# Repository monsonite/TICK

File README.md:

# TICK

A minimalist 8-bit "TTL" microcomputer based on a bit-serial ALU.

TICK is a variation of THE 16-bit MITE, bit serial machine.

The Accumulator and RAM bus have been truncated to 8-bits. However the Program Counter and the B-Register remain at 16-bits wide.

MITE provided the test bed for the discrete logic and bit-serial ALU, and TICK further refined the ALU, Program Counter and timing pulse generator into just a 6 package module, and equipped it with 8-bit parallel interfaces, suitable for connecting with a standard parallel, tristate memory data bus.

Only so much can be some in the "Digital" simulator, so now the design is being built up on breadboard, usings currently available 74HCxx series logic devices.

This will include an efficient, parallel memory sub-section, to accompany the compact TICK bit serial ALU and a means of emulating the ROM and programming the contents of the SRAM using an Arduino NANO or Raspberry Pi Pico - or clone.

The 28 ICs used are as follows:

U1	AT27C1024 	ROM

U2	74HC595		PC LOW

U3	74HC595		PC HIGH

U4	74HC165		B LOW

U5 	74HC165		B HIGH

U6	74HC4060	CLOCK DIV

U7	74HC00		SR LATCH

U8	74HC161		SEQUENCE COUNTER	

U9	74HC175		SEQUENCE FLIP FLOPS

U10	74HC138		INSTRUCTION DECODER

U11	74HC11		DECODE LOGIC	

U12	74HC85		DECODE LOGIC

U13	74HC00		DECODE LOGIC

U14	74HC283		FULL ADDER / PC INCREMENTER

U15	74HC126		ALU MUX/ PC MUX

U16	74HC74		CARRY FF / PC FF

U17	74HC299		ACCUMULATOR

U18	62256		RAM

U19	74HC74		CARRY FF / ZERO FF

U20	74HC00		RAM CONTROL

U21	74HC74		ZERO & CARRY FLAGS

U22	74HC595		SPI INPUT REGISTER

U23	74HC153		CONDITION DECODER

U24	74HC125		BUFFER

U25	74HC125		BUFFER

U26	74HC595		ROMULATOR

U27	74HC595		ROMULATOR

U28	74HC00		SPARE

## TICK - An Experimental 8-bit Bit Serial CPU.

TICK is an 8-bit, bit serial machine, with a modified Harvard architecture. This means that a ROM provides instructions and data, and volatile storage of variables is from RAM - in this case a 32K x 8-bit SRAM. ROM and RAM have separate datapaths and separate ddress buses.

TICK is based around a bit-serial architecture, consisting of an ALU, an Accumulator AC, a Memory Buffer Register B, and a Program Counter PC.

In addition to the registers there are functional blocks of the Clock Sequencer and Timing Pulse Generator CS and TPG.

The advantage of the bit-serial design is that it can easily be extended from 8-bits to 16-bits or even 32 bits with very little additional hardware.

TICK is an experimental machine, and with only about 20 ICs, it may be prototyped onto about 8 standard breadboards, or fit onto a low-cost 10 x 10 cm pcb.

Breadboard #1	ALU and Carry flip-flop

Breadboard #2	Clock oscillator, clock sequencer and timing pulse generator

Breadboard #3	Accumulator AC, Zero Detector, Zero flag, control and jump logic

Breadboard #4	Memory Buffer Register MB

Breadboard #5	Memory Address Register MA

Breadboard #6	Program Counter PC, SRAM 

Breadboard #7	Input/Output

Breadboard #8	Expansion and interface to Arduino Nano - for programming

By putting the pricipal registers AC, PC, MB on their own breadboard, it means that they can easily be extended to 16-bit or 32- bit wordlength, just by "daisy-chaining" more shift register packages in a row, and modifying the clock sequencer for a longer bit-sequence.

1. ALU and Carry Flipflop

2. Clock Sequencer and Timing Generator.

This section is the timing generator at the top 4017 decade counter and 74xx00 acting as SR latch. The actual prototype will also use a 74HC4060 14 stage counter to act as clock generator.

In the middle is the ALU. This a much tried and tested design consisting of a 74xx86 quad 2-input XOR and a pair of 74xx00 quad 2-input NANDs.

The first pair of XOR gates allow the A and B inputs to be selectively inverted for subtraction, negation and some of the logic "inverse" functions.
The next pair of XORs and NANDs form a full adder to give the Sum and Carry produced from the A and B inputs.

Three NAND gates forms a multiplexer, to choose between the Sum of A and B (A XOR B) and the Carry (A AND B). These are re-used as the logical operations.

During a logical operation, and Carry should be suppressed - hence another pair of NANDs.

Any Carry generated is retained in the 74HC74 flipflop U12A. It is then presented to the ALU when the next pair of bits are added together - so it can be included in the sum.
At the bottom in U15 and U16 is a half adder. This is used to increment the program counter after each instruction or jump to a new address. 

Any carry generated by the PC is handled in the other half of the D-type flipflop U12B.

Apart from the counters and flipflops - much of this sheet is combinational logic and could easily be replaced by a look-up table in a very small PROM.

3. Program Counter.

The 16-bit Program Counter is based around a pair of 74HC595 shift registers.

They are combined with the half adder - on the ALU sheet, so that they increment every instruction cycle, or can be loaded from serial data from the Accumulator.

The output is a 16-bit parallel word used to address the SRAM.

It could be argued that the parallel output register in the 74HC595 is doubling up as the Memory Address register MA.

The 74HC595 is a very versatile chip for interfacing to parallel RAM or parallel peripherals.

4. Memory Buffer Register MB and Switch Register SR

This is  the "Switch Register" and the "B" Shift Register which is a 74HC165 U3.

In the simulator the switches are just a convenient way to enter a byte of data - just like the front panel switches on old minicomputers.

The 74HC165 loads in the parallel word at the start of each instruction cycle and converts it to the serial pulse train Bout - which is then fed into the ALU.

5. Accumulator AC

The 8-bit Accumulator based around a single 74HC595 8-bit shift register.

If you want a 16-bit machine you just chain another 74HC595 in series with this.

It is a versatile shift register because it has a parallel output latch, so you can store the final result in parallel form - possibly for writing to a memory bus.

Fout is the 8-bit serial function that is output from the ALU.

Aout is the output of the Accumulator which is recirculated through the ALU, for example during addition.

T8 is the ninth timing pulse (they start at T0). It latches the contents of the Accumulator shift-register onto the parallel bus at the end of the completed instruction cycle.

The diode array is just an 8-input OR, it is used to detect zero.

6. Instruction Decoder.

This the Instruction Decoder - this was inspired by Marcel van Kervinck who created the Gigatron kit.

It is essentially a tiny ROM based on a diode matrix.

The instruction field is only 3 bits wide, needed to encode the 8 possible instructions.

These three bits are fed into U1 - which is a 74HC138, 3-8 line decoder.

The 3 bit input cause one of the outputs of the 74HC138 to go to logic low, the rest remaining high. From the image you can see that the 8 outputs identify the individual instruction group. Some instructions have multiple options such as choice of operands, destination etc.

LOAD

AND

OR

XOR

ADD

SUB

STORE

JUMP

Further instructions may be added later by decoding a fourth instruction bit.

In the image I apply the ADD instruction 100 in binary.

The 74HC138 selects one horizontal line of the ROM and any diodes connected to that line are pulled low. The resulting bit pattern is fed to U2 which is a 74HC540 octal inverter/driver.

This converts the instruction into a 7-bit pattern, in this case 21H.

The 7 bits define the control signals that are applied to the ALU, such as Carry, I0 and I1 select which function is chosen by the ALU output multiplexer, as follows.

00 Zero

01 XOR

10 AND

11 OR

Zero is a good way to clear the Accumulator before starting a new operation.

This circuit is entirely combinational and could be reduced to a look up table included in the same small PROM that holds the ALU.

As the ALU has 7 input control signals there are theoretically 128 possible instructions - this decoder just picks the most useful 8!

# Update 28-04-24

Some more progress on the MITE bit serial computer.

I can now load the Memory Buffer (MB) register from RAM, in parallel, and then with the one press of a single stepping switch it copies its contents into the Accumulator.

The serial output of the MB register goes directly to the serial input of the Accumulator.  The next stage is to pass this output through the ALU so that can be tested.

Below is the overall view of the device which now takes up 7, sparsely populated breadboards.

The IC count is 17 74HCxx packages and the SRAM. One of the Arduinos will be retained as the laptop interface to the computer memory.
You will have to open the image to view all the boards.

From the top:

1. LED bar displays to show the contents of the MB register (left) and the Accumulator (right).
 
2. MB (74HC165) left and Accumulator (74HC595) right.

3. SRAM Access. 62256 SRAM, 74HC245 bi-directional tristate buffer, 2 x 74HC595 ( Memory Access Register/ PC) Arduino support module to allow access to contents of RAM.
 
4. LED bar displays to show the contents of the address and data registers. MAR and external bus.
 
5. Clock pulse generator and timing. A 74HC4060 is an oscillator with a 14-stage binary divider. I am currently only clocking it at around 500Hz - so I can see what is happening. You can choose whichever clock division ratio you wish.

The 74HC4060 feeds a 74HC4017 which is a decoded, decade counter. This produces a gating signal that allows a trains of 8 clock pulses to be sent to the shift-registers to co-ordinate their data exchanges.

6. ALU termination connectors and another Arduino module to machine test the ALU.
The ALU has 8 inputs, of which 3 are the Ain, Bi and Cin from the shift registers
The Arduino is just a convenient way to dial in an instruction and test data to ensure the output is correct.

7. ALU and PC incrementer, plus any additional combinational glue logic. The PC consists of a pair of 74HC595 shift registers incremented or loaded from the MB register - in a jump condition.

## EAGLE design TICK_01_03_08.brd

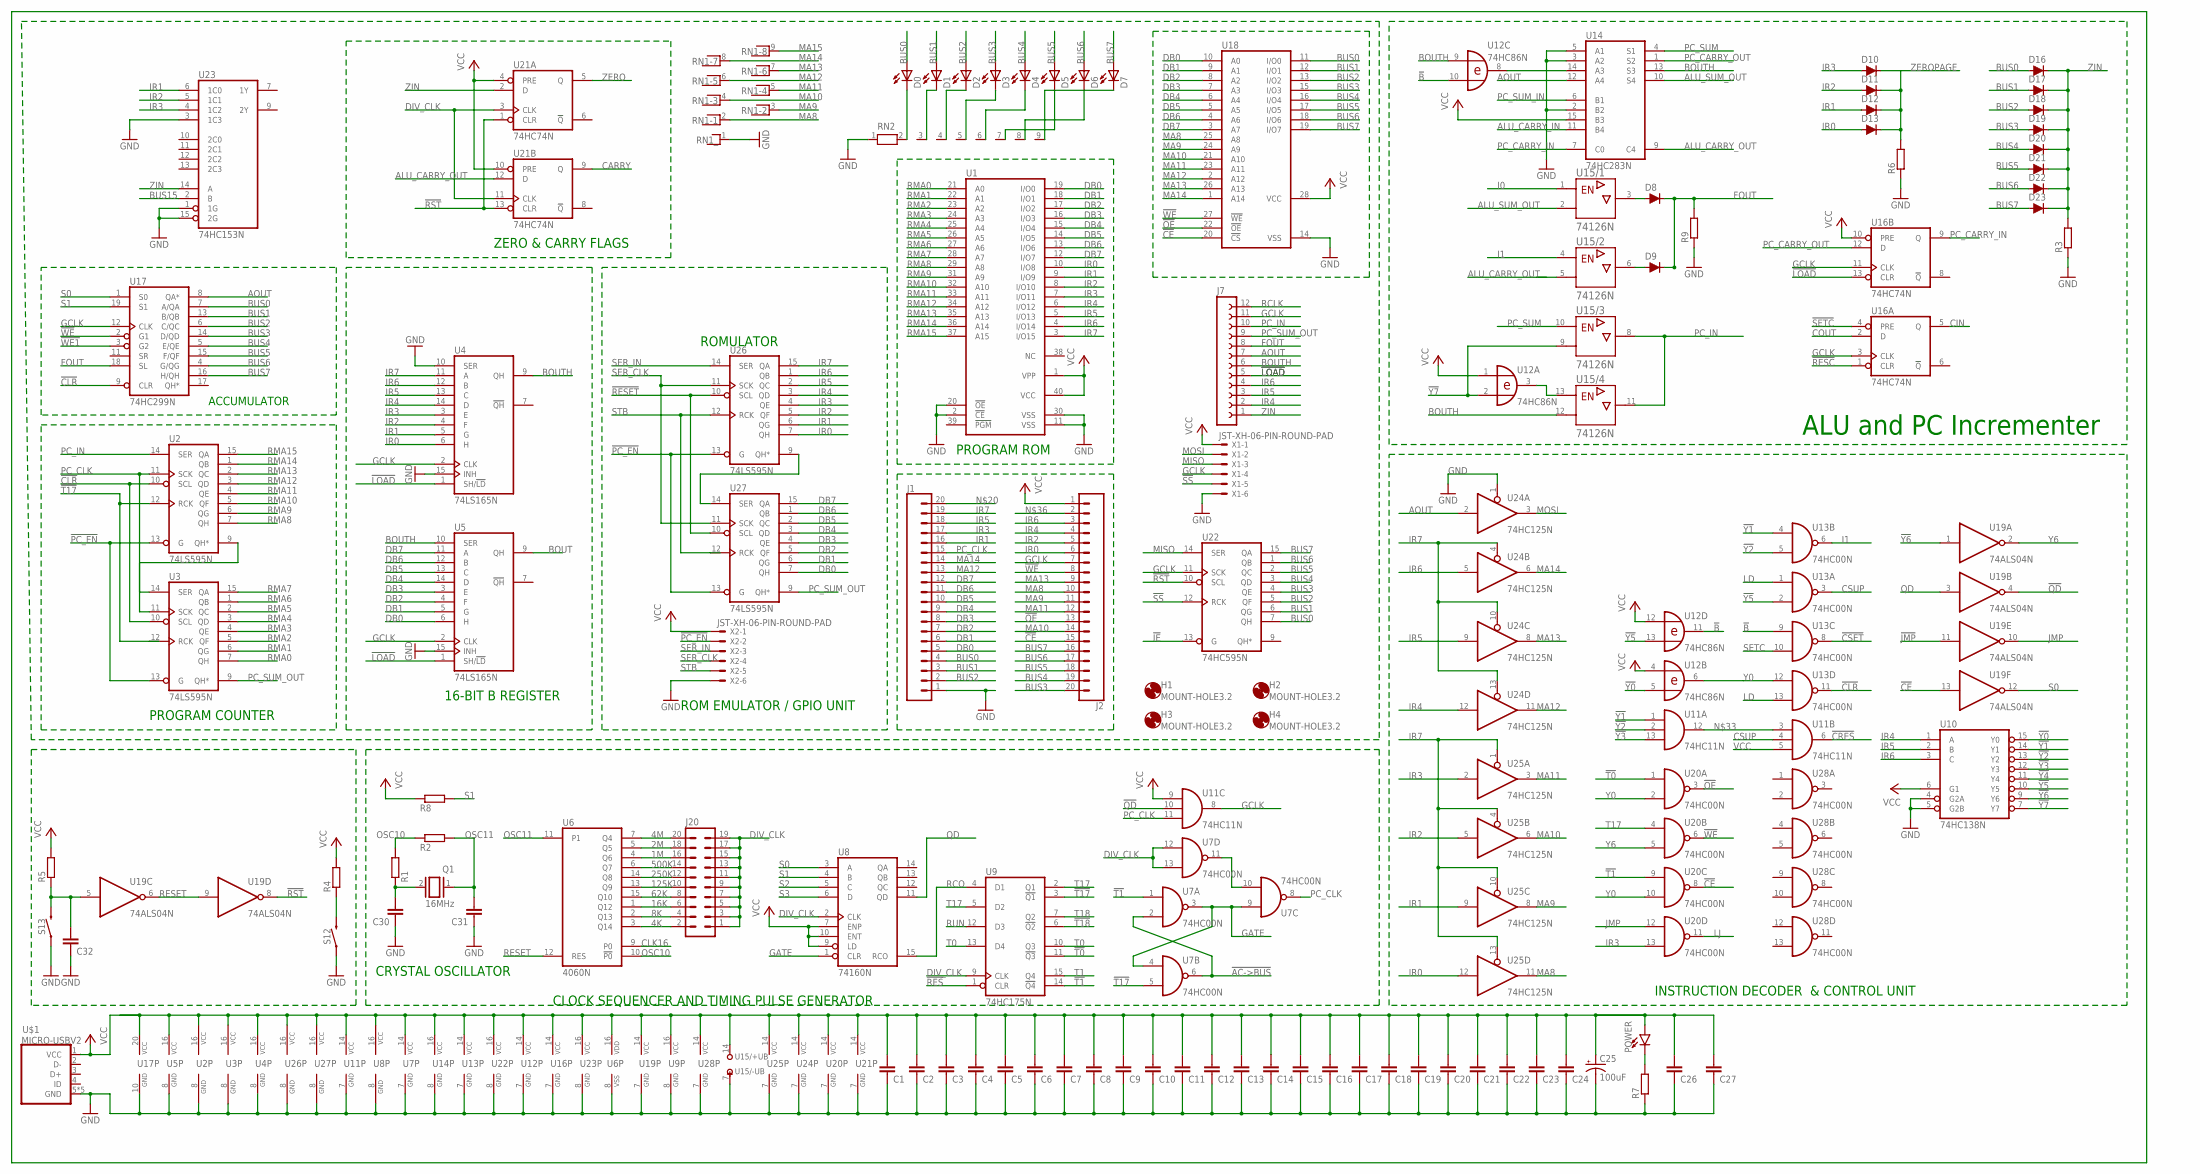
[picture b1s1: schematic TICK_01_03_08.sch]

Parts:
C1, C2, C3, C4, C5, C6, C7, C8, C9, C10, C11, C12, C13, C14, C15, C16, C17, C18, C19, C20, C21, C22, C23, C24, C26, C27, C30, C31, C32: C-EU025-024X044; C025-024X044
C25: 100uF; CPOL-RADIAL-2.5MM-6.5MM
D0, D1, D2, D3, D4, D5, D6, D7: LED3MM
D8, D9, D10, D11, D12, D13, D17, D18, D19, D20, D21, D22, D23: 200mA/100V/1V; DIODE-1N4148
D16: 200mA/100V/1V; DIODE-1N4148-KIT
H1, H2, H3, H4: MOUNT-HOLE3.2; 3,2
J1, J2: CONN_20NO_SILK_KIT; 1X20_NO_SILK_KIT
J7: FE12-1; FE12
J20: MA10-2
POWER: LED3MM; LED_3MM
Q1: 16MHz; QS
R1, R2, R3, R4, R5, R6, R7, R8, R9: R-EU_0204/5; 0204/5
RN1: RNX8; RN-9
RN2: RN08; RN-9
S12, S13: MOMENTARY-SWITCH-SPST-PTH-6.0MM; TACTILE_SWITCH_PTH_6.0MM
U1: 27C1024HG; DIL40
U2, U3, U26, U27: 74LS595N; DIL16
U4, U5: 74LS165N; DIL16
U6: 4060N; DIL16
U7, U13, U20, U28: 74HC00N; DIL14
U8: 74160N; DIL16
U9: 74HC175N; DIL16
U10: 74HC138N; DIL16
U11: 74HC11N; DIL14
U12: 74HC86N; DIL14
U14: 74HC283N; DIL16
U15: 74126N; DIL14
U16, U21: 74HC74N; DIL14
U17: 74HC299N; DIL20
U18: 62256P; DIL28-6
U19: 74ALS04N; DIL14
U22: 74HC595N; DIL16
U23: 74HC153N; DIL16
U24, U25: 74HC125N; DIL14
U$1: MICRO-USBV2; MICRO-USB-2
X1, X2: JST-XH-06-PIN-ROUND-PAD; JST-XH-06-PACKAGE-ROUND-PAD

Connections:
1M: J20.16, U6.4 (Q6)
2M: J20.18, U6.5 (Q5)
4K: J20.2, U6.3 (Q14)
4M: J20.20, U6.7 (Q4)
8K: J20.4, U6.2 (Q13)
16K: J20.6, U6.1 (Q12)
62K: J20.8, U6.15 (Q10)
125K: J20.10, U6.13 (Q9)
250K: J20.12, U6.14 (Q8)
500K: J20.14, U6.6 (Q7)
!AC->BUS: U7.2 (I1), U7.6 (O)
!B: U12.10 (I1), U12.11 (O), U13.9 (I0)
!CE: J2.15, U18.20 (!CS), U19.13 (I), U20.8 (O)
!CLR: U2.10 (SCL), U3.10 (SCL), U13.11 (O), U17.9 (CLR)
!CRES: U11.6 (O)
!CSET: U13.8 (O)
!IE: U22.13 (G)
!JMP: U19.11 (I)
!LOAD: J7.5, U4.1 (SH/!LD), U5.1 (SH/!LD), U16.13 (CLR)
!OE: J2.13, U18.22 (!OE), U20.3 (O)
!PC_EN: U2.13 (G), U3.13 (G), U26.13 (G), U27.13 (G), X2.2
!QD: U11.10 (I1), U19.4 (O)
!RES: U9.1 (CLR)
!RESC: U16.1 (CLR)
!RESET: U26.10 (SCL), U27.10 (SCL)
!RST: U19.8 (O), U21.1 (CLR), U21.13 (CLR), U22.10 (SCL)
!SETC: U16.4 (PRE)
!SS: U22.12 (RCK), X1.5
!T0: U9.11 (!Q3), U20.1 (I0)
!T1: U7.1 (I0), U9.14 (!Q4), U20.9 (I0)
!T17: U2.12 (RCK), U3.12 (RCK), U7.5 (I1), U9.3 (!Q1)
!T18: U9.6 (!Q2)
!WE: J2.8, U17.2 (G1), U18.27 (!WE), U20.6 (O)
!WE1: U17.3 (G2)
!Y0: U10.15 (Y0), U12.5 (I1)
!Y1: U10.14 (Y1), U11.1 (I0), U13.4 (I0)
!Y2: U10.13 (Y2), U11.2 (I1), U13.5 (I1)
!Y3: U10.12 (Y3), U11.13 (I2)
!Y4: U10.11 (Y4)
!Y5: U10.10 (Y5), U12.13 (I1), U13.2 (I1)
!Y6: U10.9 (Y6), U19.1 (I)
!Y7: U10.7 (Y7), U12.2 (I1), U15.9 (A)
ALU_CARRY_IN: U14.11 (B4)
ALU_CARRY_OUT: U14.9 (C4), U15.5 (A), U21.12 (D)
ALU_SUM_OUT: U14.10 (S4), U15.2 (A)
AOUT: J7.7, U14.12 (A4), U17.8 (QA*), U24.2 (I)
BOUT: U5.9 (QH)
BOUTH: J7.6, U4.9 (QH), U5.10 (SER), U12.9 (I0), U14.13 (S3), U15.12 (A)
BUS0: D0.A, D16.A, J1.4, U17.7 (A/QA), U18.11 (I/O0), U22.7 (QH)
BUS1: D1.A, D17.A, J1.3, U17.13 (B/QB), U18.12 (I/O1), U22.6 (QG)
BUS2: D2.A, D18.A, J1.2, U17.6 (C/QC), U18.13 (I/O2), U22.5 (QF)
BUS3: D3.A, D19.A, J2.20, U17.14 (D/QD), U18.15 (I/O3), U22.4 (QE)
BUS4: D4.A, D20.A, J2.19, U17.5 (E/QE), U18.16 (I/O4), U22.3 (QD)
BUS5: D5.A, D21.A, J2.18, U17.15 (F/QF), U18.17 (I/O5), U22.2 (QC)
BUS6: D6.A, D22.A, J2.17, U17.4 (G/QG), U18.18 (I/O6), U22.1 (QB)
BUS7: D7.A, D23.A, J2.16, U17.16 (H/QH), U18.19 (I/O7), U22.15 (QA)
BUS15: U23.2 (B)
CARRY: U21.9 (Q)
CIN: U16.5 (Q)
CLK16: U6.9 (P0)
COUT: U16.2 (D)
CSUP: U11.4 (I1), U13.3 (O)
DB0: J1.5, U1.19 (I/O0), U5.6 (H), U18.10 (A0), U27.7 (QH)
DB1: J1.6, U1.18 (I/O1), U5.5 (G), U18.9 (A1), U27.6 (QG)
DB2: J1.7, U1.17 (I/O2), U5.4 (F), U18.8 (A2), U27.5 (QF)
DB3: J1.8, U1.16 (I/O3), U5.3 (E), U18.7 (A3), U27.4 (QE)
DB4: J1.9, U1.15 (I/O4), U5.14 (D), U18.6 (A4), U27.3 (QD)
DB5: J1.10, U1.14 (I/O5), U5.13 (C), U18.5 (A5), U27.2 (QC)
DB6: J1.11, U1.13 (I/O6), U5.12 (B), U18.4 (A6), U27.1 (QB)
DB7: J1.12, U1.12 (I/O7), U5.11 (A), U18.3 (A7), U27.15 (QA)
DIV_CLK: J20.1, J20.3, J20.5, J20.7, J20.9, J20.11, J20.13, J20.15, J20.17, J20.19, U7.12 (I0), U7.13 (I1), U8.2 (CLK), U9.9 (CLK), U21.3 (CLK), U21.11 (CLK)
FOUT: D8.C, D9.C, J7.8, R9.2, U17.18 (SL)
GATE: U7.3 (O), U7.4 (I0), U7.9 (I0), U8.1 (CLR)
GCLK: J2.7, J7.11, U4.2 (CLK), U5.2 (CLK), U11.8 (O), U16.3 (CLK), U16.11 (CLK), U17.12 (CLK), U22.11 (SCK), X1.4
GND: C1.1, C2.1, C3.1, C4.1, C5.1, C6.1, C7.1, C8.1, C9.1, C10.1, C11.1, C12.1, C13.1, C14.1, C15.1, C16.1, C17.1, C18.1, C19.1, C20.1, C21.1, C22.1, C23.1, C24.1, C25.2 (-), C26.1, C27.1, C30.1, C31.1, C32.1, J1.1, R3.1, R6.1, R7.1, R9.1, RN1.1, RN2.1, S12.1, S13.1, U1.2 (!CE), U1.11 (VSS), U1.20 (!OE), U1.30 (VSS), U2.8 (GND), U3.8 (GND), U4.8 (GND), U4.10 (SER), U4.15 (INH), U5.8 (GND), U5.15 (INH), U6.8 (VSS), U7.7 (GND), U8.8 (GND), U9.8 (GND), U10.4 (G2A), U10.5 (G2B), U10.8 (GND), U11.7 (GND), U12.7 (GND), U13.7 (GND), U14.2 (B2), U14.3 (A2), U14.5 (A1), U14.8 (GND), U15.7 (-UB), U16.7 (GND), U17.10 (GND), U18.14 (VSS), U19.7 (GND), U20.7 (GND), U21.7 (GND), U22.8 (GND), U23.1 (1G), U23.3 (1C3), U23.8 (GND), U23.15 (2G), U24.1 (OE), U24.7 (GND), U25.7 (GND), U26.8 (GND), U27.8 (GND), U28.7 (GND), U$1.5 (GND), U$1.P$1 (GND), U$1.P$2 (GND), U$1.P$3 (GND), U$1.P$4 (GND), X1.6, X2.6
I0: U15.1 (G)
I1: U13.6 (O), U15.4 (G)
IR0: D13.A, J2.6, U1.10 (I/O8), U4.6 (H), U25.12 (I), U26.7 (QH)
IR1: D12.A, J1.16, U1.9 (I/O9), U4.5 (G), U23.6 (1C0), U25.9 (I), U26.6 (QG)
IR2: D11.A, J2.5, U1.8 (I/O10), U4.4 (F), U23.5 (1C1), U25.5 (I), U26.5 (QF)
IR3: D10.A, J1.17, U1.7 (I/O11), U4.3 (E), U20.13 (I1), U23.4 (1C2), U25.2 (I), U26.4 (QE)
IR4: J2.4, J7.2, U1.6 (I/O12), U4.14 (D), U10.1 (A), U24.12 (I), U26.3 (QD)
IR5: J1.18, J7.3, U1.5 (I/O13), U4.13 (C), U10.2 (B), U24.9 (I), U26.2 (QC)
IR6: J2.3, J7.4, U1.4 (I/O14), U4.12 (B), U10.3 (C), U24.5 (I), U26.1 (QB)
IR7: J1.19, U1.3 (I/O15), U4.11 (A), U24.4 (OE), U24.10 (OE), U24.13 (OE), U25.1 (OE), U25.4 (OE), U25.10 (OE), U25.13 (OE), U26.15 (QA)
JMP: U19.10 (O), U20.12 (I0)
LD: U13.1 (I0), U13.13 (I1)
LJ: U20.11 (O)
MA8: J2.10, RN1.2, U18.25 (A8), U25.11 (O)
MA9: J2.11, RN1.3, U18.24 (A9), U25.8 (O)
MA10: J2.14, RN1.4, U18.21 (A10), U25.6 (O)
MA11: J2.12, RN1.5, U18.23 (A11), U25.3 (O)
MA12: J1.13, RN1.6, U18.2 (A12), U24.11 (O)
MA13: J2.9, RN1.7, U18.26 (A13), U24.8 (O)
MA14: J1.14, RN1.8, U18.1 (A14), U24.6 (O)
MA15: RN1.9
MISO: U22.14 (SER), X1.3
MOSI: U24.3 (O), X1.2
unnamed: D0.K (C), RN2.2
unnamed: D1.K (C), RN2.3
unnamed: U7.10 (I1), U7.11 (O)
unnamed: D2.K (C), RN2.4
unnamed: D8.A, U15.3 (Y)
unnamed: R4.1, S12.3 (2)
unnamed: C32.2, R5.1, S13.3 (2), U19.5 (I)
unnamed: POWER.K (C), R7.2
unnamed: U12.8 (O), U14.14 (A3)
unnamed: D9.A, U15.6 (Y)
unnamed: D3.K (C), RN2.5
unnamed: D4.K (C), RN2.6
unnamed: D5.K (C), RN2.7
unnamed: D6.K (C), RN2.8
unnamed: D7.K (C), RN2.9
unnamed: U2.9 (QH*), U3.14 (SER)
unnamed: U11.3 (I0), U11.12 (O)
unnamed: U26.9 (QH*), U27.14 (SER)
unnamed: U12.3 (O), U15.13 (G)
unnamed: C30.2, Q1.2, R1.1
OSC10: R1.2, R2.1, U6.10 (!P0)
OSC11: C31.2, Q1.1, R2.2, U6.11 (P1)
PC_CARRY_IN: U14.7 (C0), U16.9 (Q)
PC_CARRY_OUT: U14.1 (S2), U16.12 (D)
PC_CLK: J1.15, U2.11 (SCK), U3.11 (SCK), U7.8 (O), U11.11 (I2)
PC_IN: J7.10, U2.14 (SER), U15.8 (Y), U15.11 (Y)
PC_SUM: U14.4 (S1), U15.10 (G)
PC_SUM_IN: U14.6 (B1)
PC_SUM_OUT: J7.9, U3.9 (QH*), U27.9 (QH*)
QD: U8.11 (QD), U19.3 (I)
RCLK: J7.12
RCO: U8.15 (RCO), U9.4 (D1)
RESET: U6.12 (RES), U19.6 (O), U19.9 (I)
RMA0: U1.21 (A0), U3.7 (QH)
RMA1: U1.22 (A1), U3.6 (QG)
RMA2: U1.23 (A2), U3.5 (QF)
RMA3: U1.24 (A3), U3.4 (QE)
RMA4: U1.25 (A4), U3.3 (QD)
RMA5: U1.26 (A5), U3.2 (QC)
RMA6: U1.27 (A6), U3.1 (QB)
RMA7: U1.28 (A7), U3.15 (QA)
RMA8: U1.29 (A8), U2.7 (QH)
RMA9: U1.31 (A9), U2.6 (QG)
RMA10: U1.32 (A10), U2.5 (QF)
RMA11: U1.33 (A11), U2.4 (QE)
RMA12: U1.34 (A12), U2.3 (QD)
RMA13: U1.35 (A13), U2.2 (QC)
RMA14: U1.36 (A14), U2.1 (QB)
RMA15: U1.37 (A15), U2.15 (QA)
RUN: U9.12 (D3)
S0: U8.3 (A), U17.1 (S0), U19.12 (O)
S1: R8.2, U8.4 (B), U17.19 (S1)
S2: U8.5 (C)
S3: U8.6 (D)
SER_CLK: U26.11 (SCK), U27.11 (SCK), X2.4
SER_IN: U26.14 (SER), X2.3
SETC: U13.10 (I1)
STB: U26.12 (RCK), U27.12 (RCK), X2.5
T0: U9.10 (Q3), U9.13 (D4)
T1: U9.15 (Q4)
T17: U9.2 (Q1), U9.5 (D2), U20.4 (I0)
T18: U9.7 (Q2)
VCC: C1.2, C2.2, C3.2, C4.2, C5.2, C6.2, C7.2, C8.2, C9.2, C10.2, C11.2, C12.2, C13.2, C14.2, C15.2, C16.2, C17.2, C18.2, C19.2, C20.2, C21.2, C22.2, C23.2, C24.2, C25.1 (+), C26.2, C27.2, J2.1, POWER.A, R4.2, R5.2, R8.1, U1.1 (VPP), U1.40 (VCC), U2.16 (VCC), U3.16 (VCC), U4.16 (VCC), U5.16 (VCC), U6.16 (VDD), U7.14 (VCC), U8.7 (ENP), U8.9 (LD), U8.10 (ENT), U8.16 (VCC), U9.16 (VCC), U10.6 (G1), U10.16 (VCC), U11.5 (I2), U11.9 (I0), U11.14 (VCC), U12.1 (I0), U12.4 (I0), U12.12 (I0), U12.14 (VCC), U13.14 (VCC), U14.15 (B3), U14.16 (VCC), U15.14 (+UB), U16.10 (PRE), U16.14 (VCC), U17.20 (VCC), U18.28 (VCC), U19.14 (VCC), U20.14 (VCC), U21.4 (PRE), U21.10 (PRE), U21.14 (VCC), U22.16 (VCC), U23.16 (VCC), U24.14 (VCC), U25.14 (VCC), U26.16 (VCC), U27.16 (VCC), U28.14 (VCC), U$1.1 (VCC), X1.1, X2.1
Y0: U13.12 (I0), U20.2 (I1), U20.10 (I1)
Y6: U19.2 (O), U20.5 (I1)
ZERO: U21.5 (Q)
ZEROPAGE: D10.C, D11.C, D12.C, D13.C, R6.2
ZIN: D16.C, D17.C, D18.C, D19.C, D20.C, D21.C, D22.C, D23.C, J7.1, R3.2, U21.2 (D), U23.14 (A)

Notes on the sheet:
ALU and PC Incrementer
CLOCK SEQUENCER AND TIMING PULSE GENERATOR
CRYSTAL OSCILLATOR
ZERO & CARRY FLAGS
INSTRUCTION DECODER & CONTROL UNIT
ROM EMULATOR / GPIO UNIT
PROGRAM ROM
ACCUMULATOR
16-BIT B REGISTER
PROGRAM COUNTER
ROMULATOR

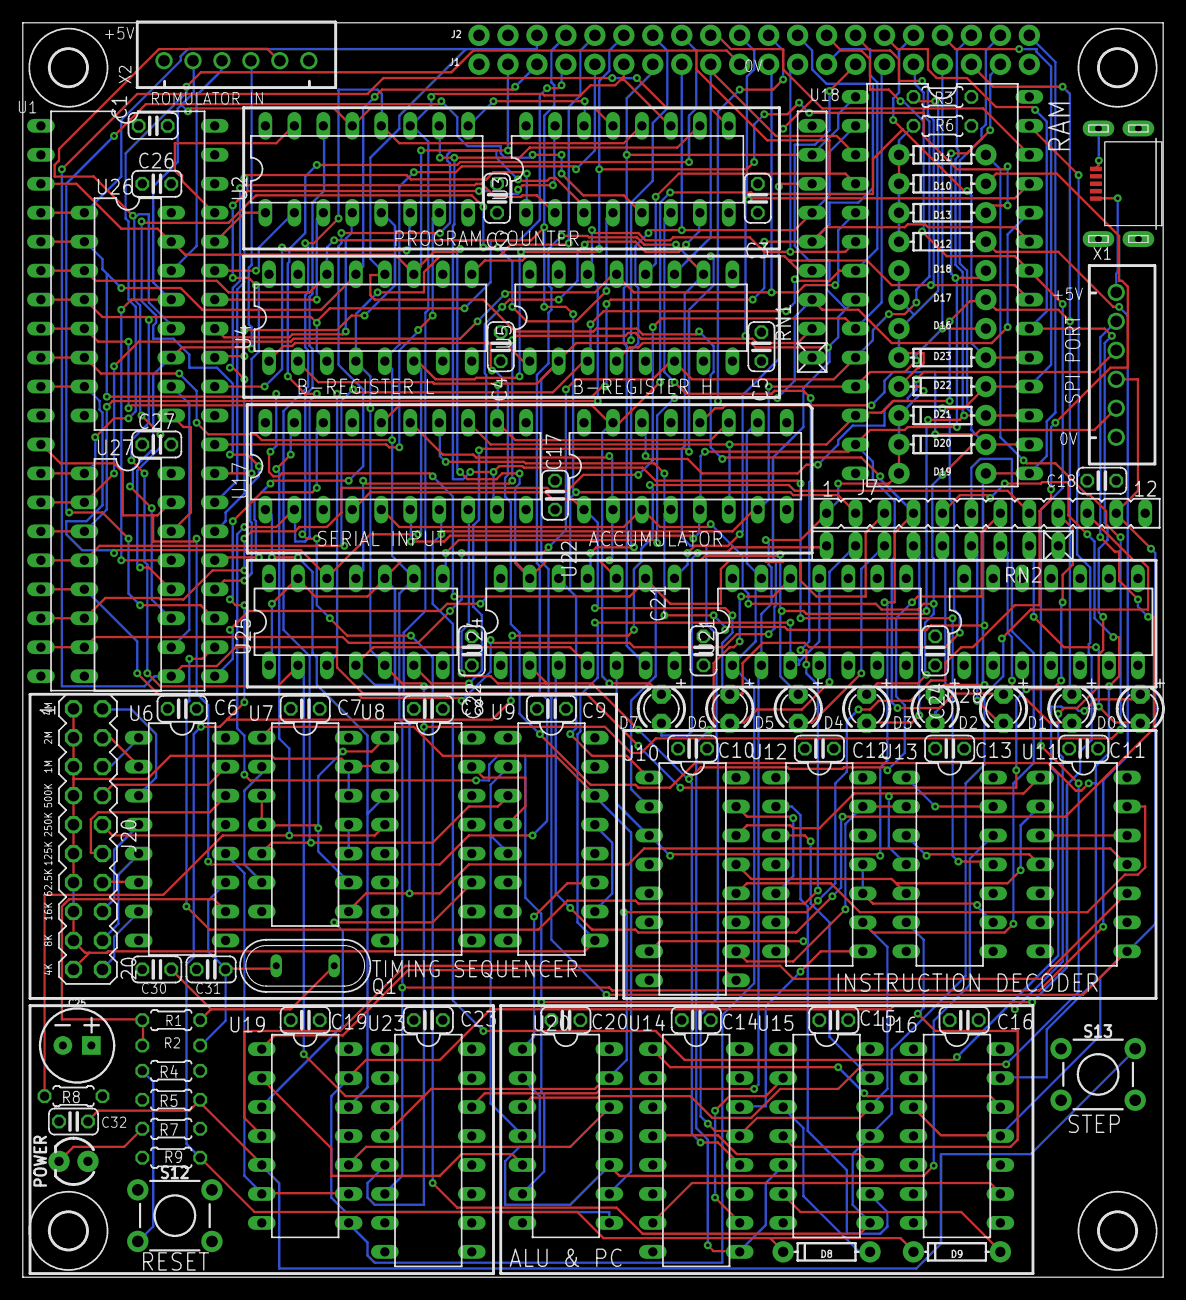
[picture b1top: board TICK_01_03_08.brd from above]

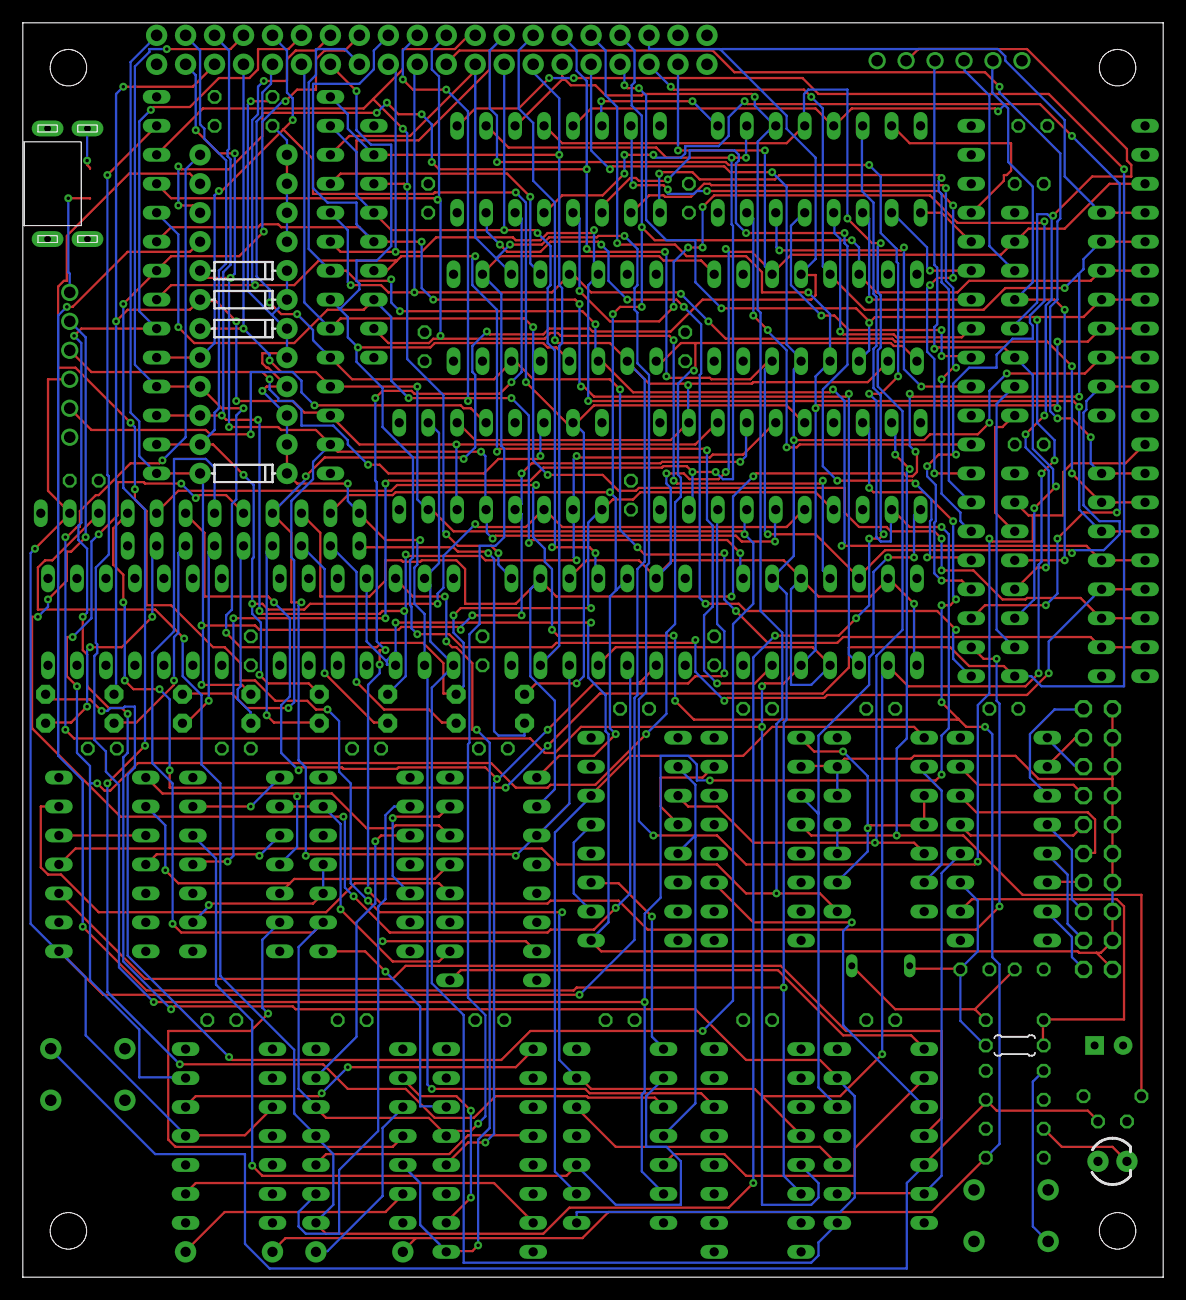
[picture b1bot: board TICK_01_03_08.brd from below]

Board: 4 copper layers, 100.0 x 110.0 mm, 106 parts (5 on the bottom side), 137 nets.

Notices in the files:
parts and their libraries:
SparkFun-DiscreteSemi: Licensing: Creative Commons ShareAlike 4.0 International - https://creativecommons.org/licenses/by-sa/4.0
